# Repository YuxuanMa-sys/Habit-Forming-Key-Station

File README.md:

# Habit Forming Key Station

# Problem

People have a difficult time building habits. Specifically, a common issue that many have is losing or misplacing their keys/wallet whenever they enter their place of residence. If they were accustomed to placing and grabbing their keys from a specific designated location, then the likelihood of losing their keys and wallet would be significantly low.

# Solution

Our solution utilizes negative reinforcement to build positive habits for its users. We will build a designated station for placing one’s keys, or any small item of their choosing, when entering or leaving their home. It will begin detecting the proximity of the keys a few minutes after the keys have initially been removed from the dish, indicating the resident is not home. Once the resident returns home with the keys, a sensor should detect its presence with an RFID tag and continue ringing an alarm through a speaker until the keys are placed correctly. There will be a pressure sensor at the bottom of the dish that will indicate whether the keys have been put into the device. Our solution will have 5 subsystems: proximity detection, control and processing, alarm, confirmation, and power. 

Team members:

- [Ali Husain]
- [Cedric Mathew]
- [Marsh Ma]

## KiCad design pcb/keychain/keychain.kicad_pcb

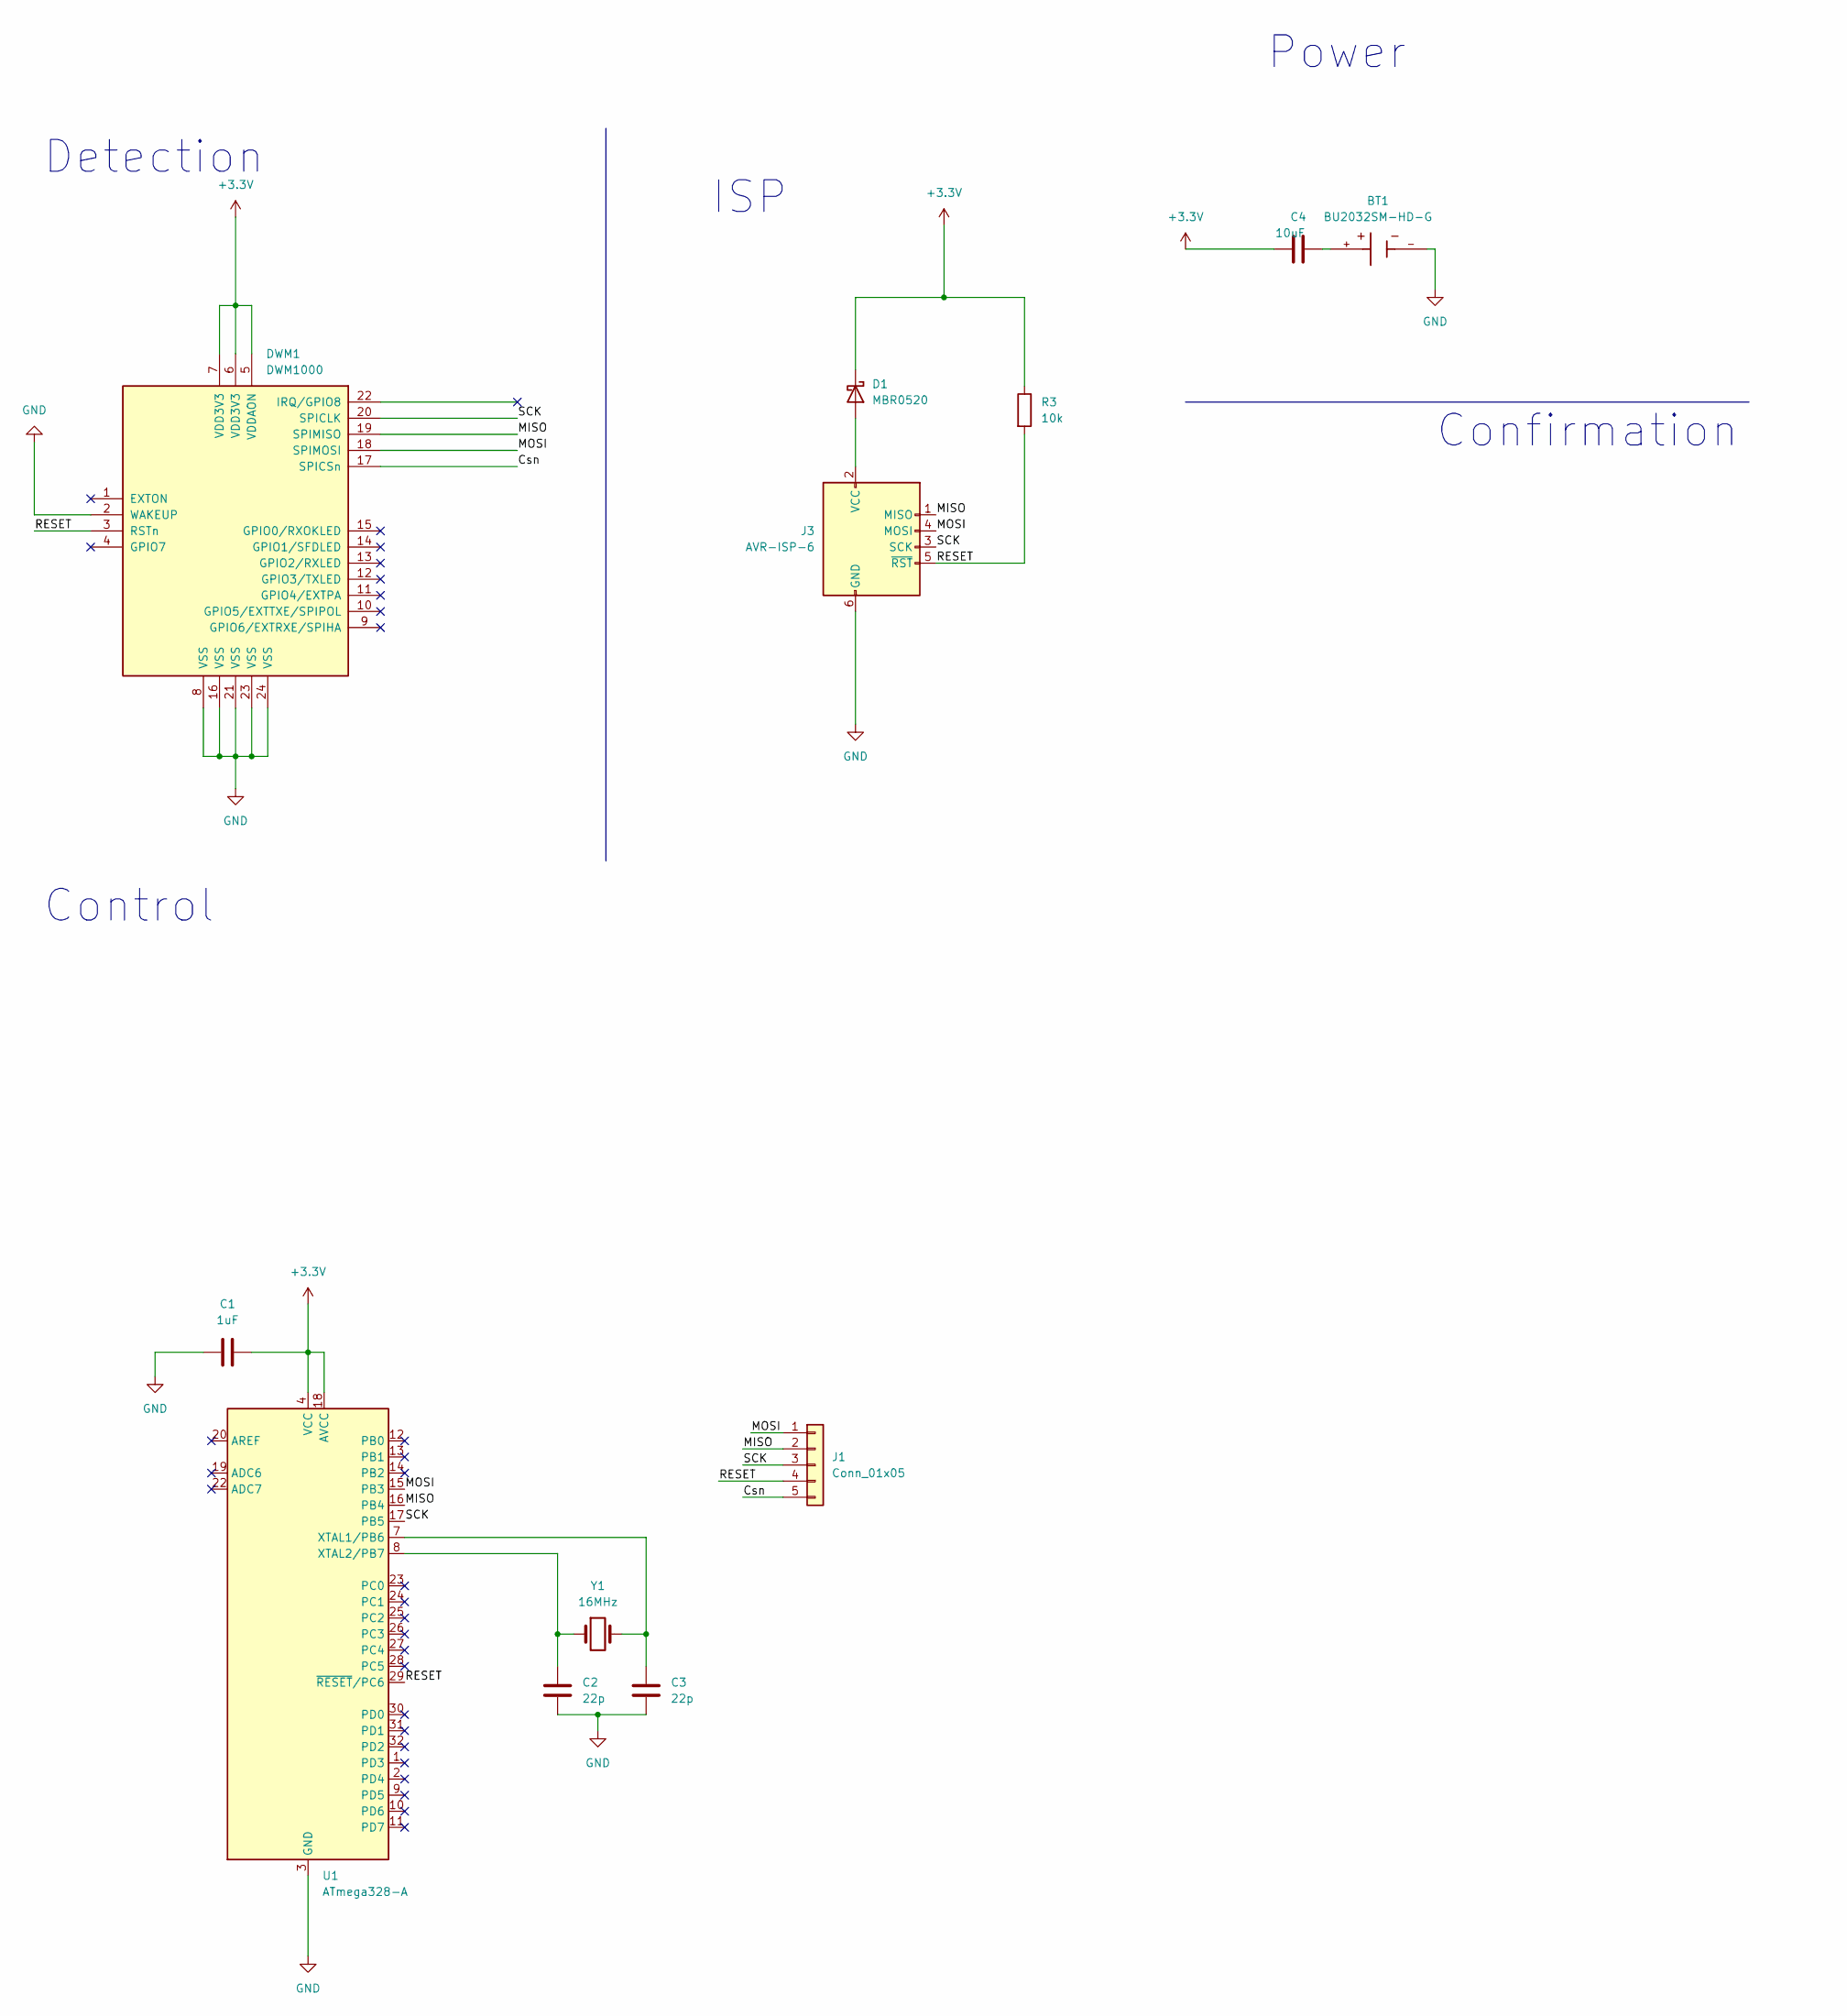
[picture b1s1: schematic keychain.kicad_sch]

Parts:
BT1: BU2032SM-HD-G; BAT_BU2032SM-HD-G; PARTREV 01/27/17
C1: 1uF; C_0805_2012Metric_Pad1.18x1.45mm_HandSolder
C2, C3: 22p; C_0805_2012Metric_Pad1.18x1.45mm_HandSolder
C4: 10uF; C_0805_2012Metric_Pad1.18x1.45mm_HandSolder
D1: MBR0520; D_SOD-123
DWM1: DWM1000
J1: Conn_01x05; Molex_KK-254_AE-6410-05A_1x05_P2.54mm_Vertical
J3: AVR-ISP-6; IDC-Header_2x03_P2.54mm_Vertical
R3: 10k; R_0805_2012Metric_Pad1.20x1.40mm_HandSolder
U1: ATmega328-A; TQFP-32_7x7mm_P0.8mm
Y1: 16MHz; Crystal_HC49-U_Vertical

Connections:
+3.3V: C1.2, C4.1, D1.1 (K), DWM1.5 (VDDAON), DWM1.6 (VDD3V3), DWM1.7 (VDD3V3), R3.1, U1.4 (VCC), U1.6 (VCC), U1.18 (AVCC)
/Csn: DWM1.17 (SPICSn), J1.5
/MISO: DWM1.19 (SPIMISO), J1.2, J3.1 (MISO), U1.16 (PB4)
/MOSI: DWM1.18 (SPIMOSI), J1.1, J3.4 (MOSI), U1.15 (PB3)
/RESET: DWM1.3 (RSTn), J1.4, J3.5 (~RST), R3.2, U1.29 (~RESET/PC6)
/SCK: DWM1.20 (SPICLK), J1.3, J3.3 (SCK), U1.17 (PB5)
GND: BT1.-, C1.1, C2.2, C3.2, DWM1.2 (WAKEUP), DWM1.8 (VSS), DWM1.16 (VSS), DWM1.21 (VSS), DWM1.23 (VSS), DWM1.24 (VSS), J3.6 (GND), U1.3 (GND), U1.5 (GND), U1.21 (GND)
unnamed: BT1.+, C4.2
unnamed: D1.2 (A), J3.2 (VCC)
unnamed: C3.1, U1.7 (XTAL1/PB6), Y1.2
unnamed: C2.1, U1.8 (XTAL2/PB7), Y1.1

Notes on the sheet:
Power
ISP
Detection
Confirmation
Control

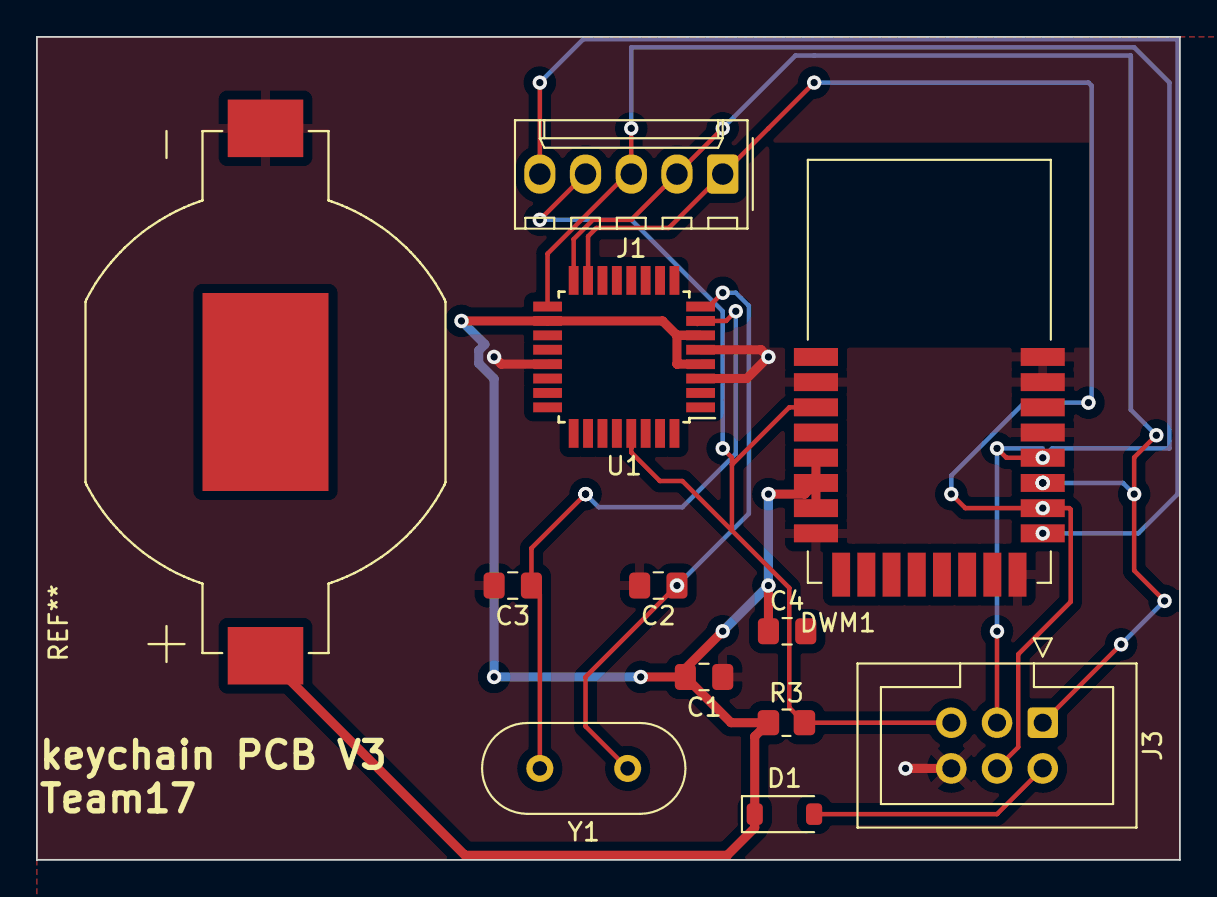
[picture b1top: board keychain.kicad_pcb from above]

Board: 2 copper layers, 63.5 x 45.7 mm, 11 parts (0 on the bottom side), 10 nets.

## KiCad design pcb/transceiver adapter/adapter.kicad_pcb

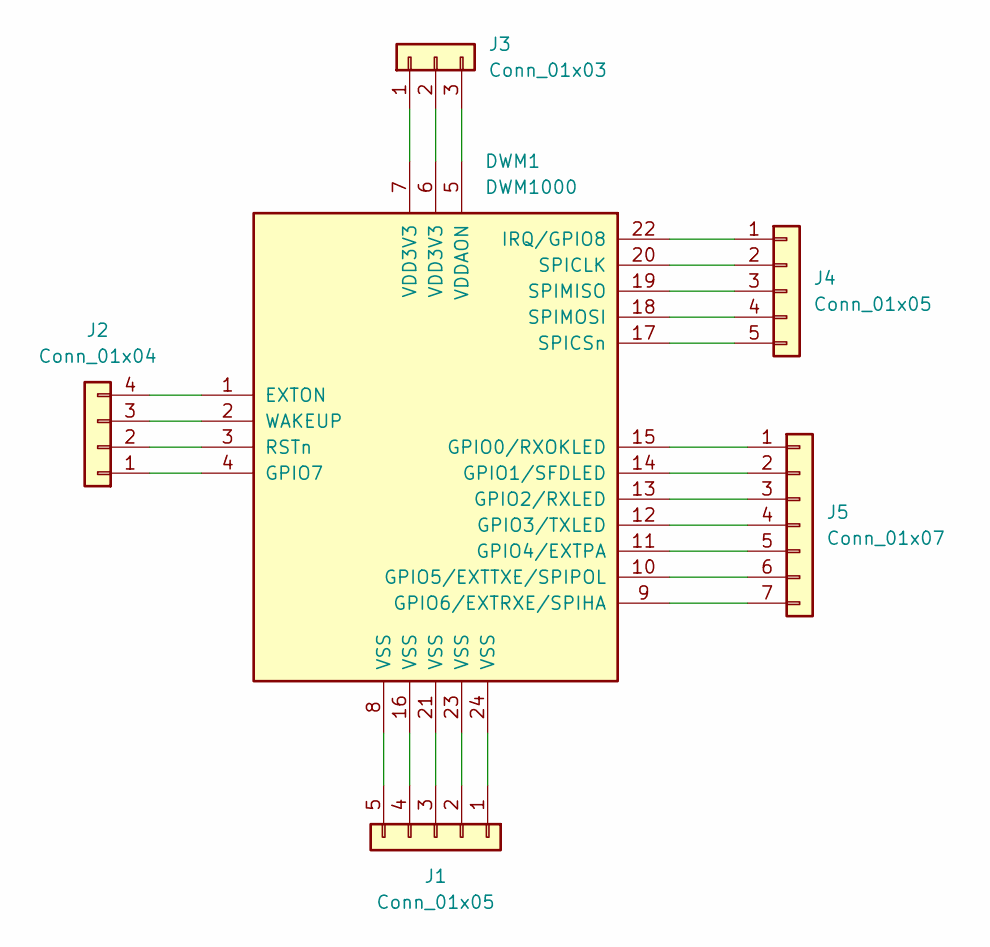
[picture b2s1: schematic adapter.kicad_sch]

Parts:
DWM1: DWM1000
J1, J4: Conn_01x05; Molex_KK-254_AE-6410-05A_1x05_P2.54mm_Vertical
J2: Conn_01x04; Molex_KK-254_AE-6410-04A_1x04_P2.54mm_Vertical
J3: Conn_01x03; Molex_KK-254_AE-6410-03A_1x03_P2.54mm_Vertical
J5: Conn_01x07; Molex_KK-254_AE-6410-07A_1x07_P2.54mm_Vertical

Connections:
unnamed: DWM1.1 (EXTON), J2.4
unnamed: DWM1.15 (GPIO0/RXOKLED), J5.1
unnamed: DWM1.14 (GPIO1/SFDLED), J5.2
unnamed: DWM1.13 (GPIO2/RXLED), J5.3
unnamed: DWM1.12 (GPIO3/TXLED), J5.4
unnamed: DWM1.11 (GPIO4/EXTPA), J5.5
unnamed: DWM1.10 (GPIO5/EXTTXE/SPIPOL), J5.6
unnamed: DWM1.9 (GPIO6/EXTRXE/SPIHA), J5.7
unnamed: DWM1.4 (GPIO7), J2.1
unnamed: DWM1.22 (IRQ/GPIO8), J4.1
unnamed: DWM1.3 (RSTn), J2.2
unnamed: DWM1.20 (SPICLK), J4.2
unnamed: DWM1.17 (SPICSn), J4.5
unnamed: DWM1.19 (SPIMISO), J4.3
unnamed: DWM1.18 (SPIMOSI), J4.4
unnamed: DWM1.5 (VDDAON), J3.3
unnamed: DWM1.2 (WAKEUP), J2.3
unnamed: DWM1.24 (VSS), J1.1
unnamed: DWM1.23 (VSS), J1.2
unnamed: DWM1.21 (VSS), J1.3
unnamed: DWM1.16 (VSS), J1.4
unnamed: DWM1.8 (VSS), J1.5
unnamed: DWM1.7 (VDD3V3), J3.1
unnamed: DWM1.6 (VDD3V3), J3.2

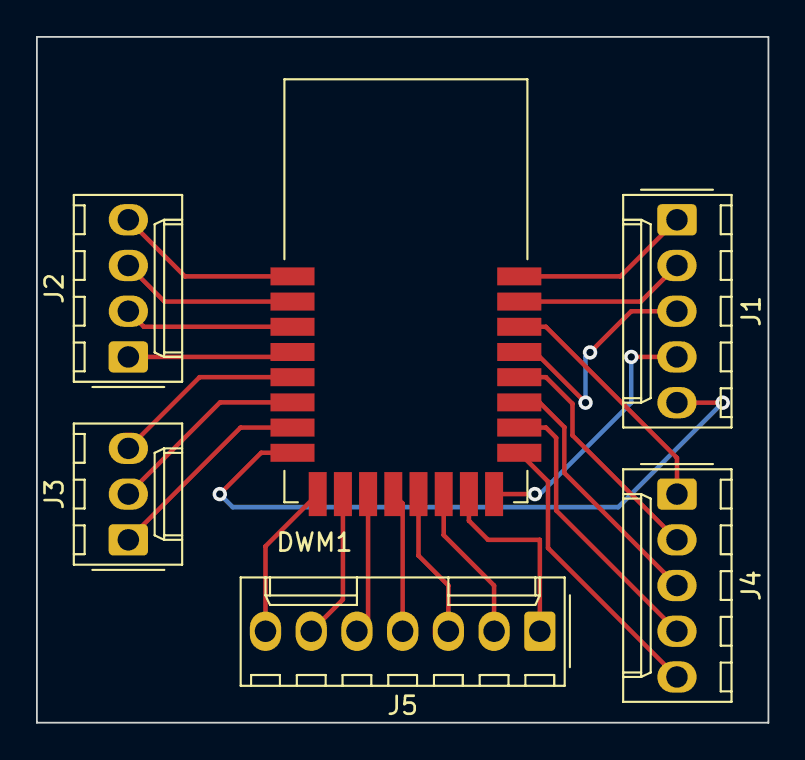
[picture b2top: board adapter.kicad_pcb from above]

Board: 2 copper layers, 40.6 x 38.1 mm, 6 parts (0 on the bottom side), 24 nets.

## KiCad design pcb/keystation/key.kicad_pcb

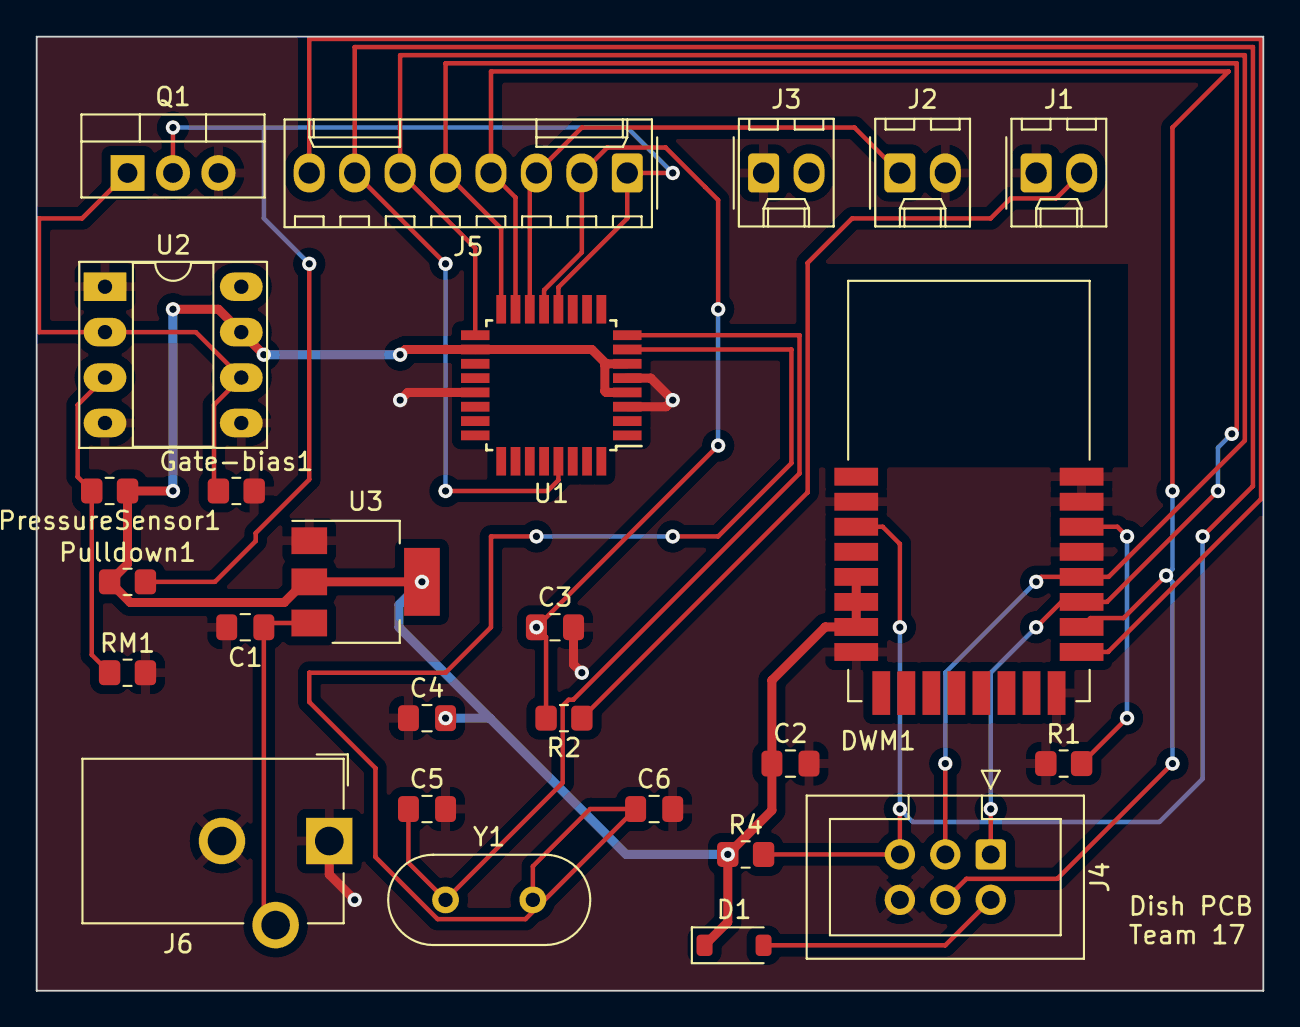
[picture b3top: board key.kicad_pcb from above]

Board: 2 copper layers, 68.6 x 53.3 mm, 26 parts (0 on the bottom side), 17 nets.

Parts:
C1, C2: 10uF; C_0805_2012Metric_Pad1.18x1.45mm_HandSolder
C3, C4: 1uF; C_0805_2012Metric_Pad1.18x1.45mm_HandSolder
C5, C6: 22p; C_0805_2012Metric_Pad1.18x1.45mm_HandSolder
D1: MBR0520; D_SOD-123
DWM1: DWM1000
Gate-bias1: 1k; R_0805_2012Metric_Pad1.20x1.40mm_HandSolder
J1: Button; Molex_KK-254_AE-6410-02A_1x02_P2.54mm_Vertical
J2: speaker; Molex_KK-254_AE-6410-02A_1x02_P2.54mm_Vertical
J3: Vin; Molex_KK-254_AE-6410-02A_1x02_P2.54mm_Vertical
J4: AVR-ISP-6; IDC-Header_2x03_P2.54mm_Vertical
J5: Conn_01x08; Molex_KK-254_AE-6410-08A_1x08_P2.54mm_Vertical
J6: Barrel_Jack_Switch; BarrelJack_CUI_PJ-102AH_Horizontal
PressureSensor1: FSR; R_0805_2012Metric_Pad1.20x1.40mm_HandSolder
Pulldown1: 1k; R_0805_2012Metric_Pad1.20x1.40mm_HandSolder
Q1: IRF540N; TO-220-3_Vertical
R1: 100; R_0805_2012Metric_Pad1.20x1.40mm_HandSolder
R2, R4: 10k; R_0805_2012Metric_Pad1.20x1.40mm_HandSolder
RM1: 10k; R_0805_2012Metric_Pad1.20x1.40mm_HandSolder
U1: ATmega328-A; TQFP-32_7x7mm_P0.8mm
U2: LM741; DIP-8_W7.62mm_Socket_LongPads
U3: LM1117MP-3.3; SOT-223-3_TabPin2
Y1: 16MHz; Crystal_HC49-U_Vertical

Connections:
+3.3V: C2.1, C4.2, D1.1 (K), DWM1.5 (VDDAON), DWM1.6 (VDD3V3), DWM1.7 (VDD3V3), PressureSensor1.1, Pulldown1.1, R4.1, U1.4 (VCC), U1.6 (VCC), U1.18 (AVCC), U2.7 (V+), U3.2 (VO)
/Csn: DWM1.17 (SPICSn), J5.8
/MISO: DWM1.19 (SPIMISO), J4.1 (MISO), J5.5, U1.16 (PB4)
/MOSI: DWM1.18 (SPIMOSI), J4.4 (MOSI), J5.4, U1.15 (PB3)
/RESET: DWM1.3 (RSTn), J4.5 (~RST), J5.7, R4.2, U1.29 (~RESET/PC6)
/SCK: DWM1.20 (SPICLK), J4.3 (SCK), J5.6, U1.17 (PB5)
/alarm: J2.1, J5.3, U1.14 (PB2)
/button: C3.1, J5.2, R2.2, U1.13 (PB1)
/confirmation: J5.1, Pulldown1.2, Q1.2 (D), U1.12 (PB0)
GND: C1.2, C2.2, C3.2, C4.1, C5.2, C6.2, DWM1.2 (WAKEUP), DWM1.8 (VSS), DWM1.16 (VSS), DWM1.21 (VSS), DWM1.23 (VSS), DWM1.24 (VSS), Gate-bias1.2, J1.1, J2.2, J3.1, J4.6 (GND), J6.1, J6.2, Q1.3 (S), R1.1, RM1.2, U1.3 (GND), U1.5 (GND), U1.21 (GND), U2.1 (NULL), U2.4 (V-), U2.5 (NULL), U3.1 (GND)
unnamed: D1.2 (A), J4.2 (VCC)
unnamed: J1.2, R2.1
unnamed: Gate-bias1.1, Q1.1 (G), U2.2 (-), U2.6
unnamed: C6.1, U1.7 (XTAL1/PB6), Y1.2
unnamed: C5.1, U1.8 (XTAL2/PB7), Y1.1
unnamed: PressureSensor1.2, RM1.1, U2.3 (+)
unnamed: C1.1, J6.3, U3.3 (VI)

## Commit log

2024-02-29 add pcb
2024-03-19 keystation pcb
2024-03-19 keychain pcb
2024-03-26 update pcb
2024-03-26 generated week 3 gerbers
2024-03-28 starter station code
2024-03-30 updated code
2024-03-31 adapter added
2024-04-03 dish pcb updated
2024-04-15 debugging ranging code
2024-04-16 working code
2024-05-02 notebook
2024-05-03 lab notebook final push
2024-05-03 final push
